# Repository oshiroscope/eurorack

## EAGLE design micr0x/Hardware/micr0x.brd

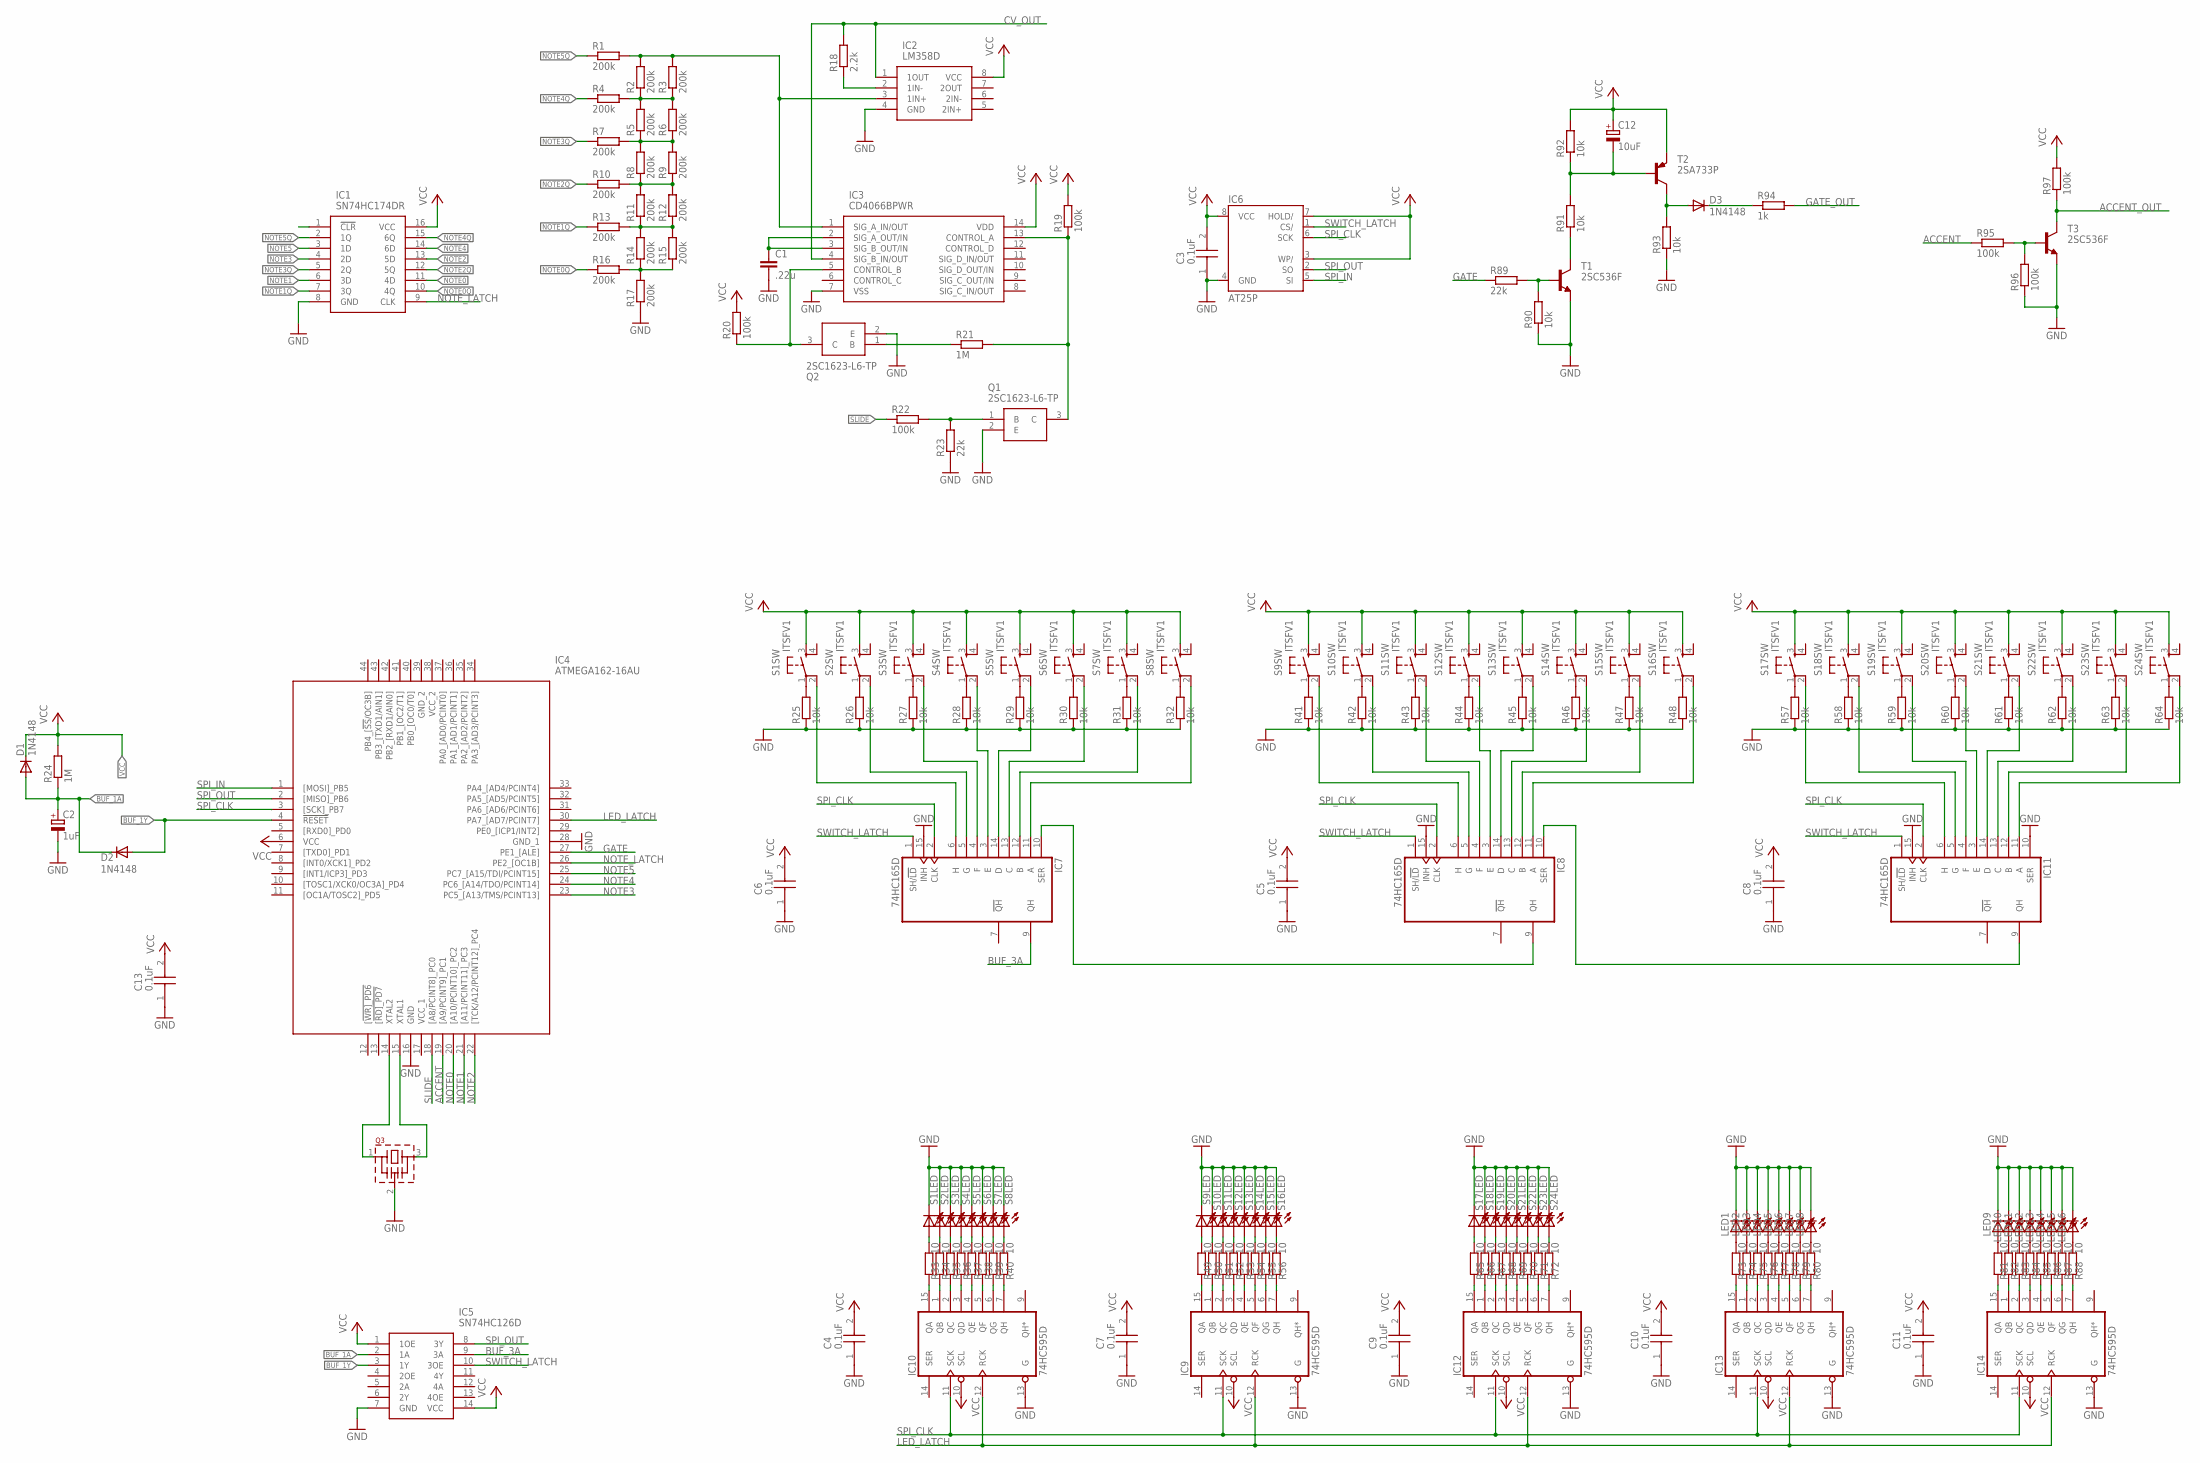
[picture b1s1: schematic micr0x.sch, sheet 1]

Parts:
C1: .22u; C075-032X103; MOUSER_PART_NUMBER QYX2A224KTP
C2: 1uF; E2-5; MOUSER_PART_NUMBER 140-REA1R0M2CBK0511P
C3, C4, C5, C6, C7, C8, C9, C10, C11, C13: 0.1uF; CAPC1608X90N
C12: 10uF; E2-5
D1, D2, D3: 1N4148; DO35-7
IC1: SN74HC174DR; SOIC127P600X175-16N
IC2: LM358D; SOIC127P600X175-8N
IC3: CD4066BPWR; SOP65P640X120-14N
IC4: ATMEGA162-16AU; QFP80P1200X1200X120-44N
IC5: SN74HC126D; SOIC127P600X175-14N
IC6: AT25P; DIL08
IC7, IC8, IC11: 74HC165D; SO16
IC9, IC10, IC12, IC13, IC14: 74HC595D; SO16
LED1, LED2, LED3, LED4, LED5, LED6, LED7, LED8, LED9, LED10, LED11, LED12, LED13, LED14, LED15, LED16: LED3MM
Q1, Q2: 2SC1623-L6-TP; SOT96P237X112-3N
Q3: CSTLS_X
R1, R2, R3, R4, R5, R6, R7, R8, R9, R10, R11, R12, R13, R14, R15, R16, R17: 200k; R0603; MOUSER_PART_NUMBER RCS0603200KFKEA
R18: 2.2k; R0603; MOUSER_PART_NUMBER RCS06032K20JNEA
R19, R20, R22: 100k; R0603; MOUSER_PART_NUMBER RCS0603100KJNEA
R21, R24: 1M; R0603; MOUSER_PART_NUMBER RCS06031M00JNEA
R23: 22k; R0603; MOUSER_PART_NUMBER RCS060322K0JNEA
R25, R26, R27, R28, R29, R30, R31, R32, R41, R42, R43, R44, R45, R46, R47, R48, R57, R58, R59, R60, R61, R62, R63, R64, R90, R91, R92, R93: 10k; R0603; MOUSER_PART_NUMBER RCS060310K0JNEA
R33, R34, R35, R36, R37, R38, R39, R40, R49, R50, R51, R52, R53, R54, R55, R56, R65, R66, R67, R68, R69, R70, R71, R72, R73, R74, R75, R76, R77, R78, R79, R80, R81, R82, R83, R84, R85, R86, R87, R88: 10; R0603; MOUSER_PART_NUMBER RCS0603200KFKEA
R89: 22k; R0603; MOUSER_PART_NUMBER RCS060310K0JNEA
R94: 1k; R0603; MOUSER_PART_NUMBER RCS060310K0JNEA
R95, R96, R97: 100k; R0603; MOUSER_PART_NUMBER RCS060310K0JNEA
S1, S2, S3, S4, S5, S6, S7, S8, S9, S10, S11, S12, S13, S14, S15, S16, S17, S18, S19, S20, S21, S22, S23, S24: ITSFV1
T1, T3: 2SC536F; TO92
T2: 2SA733P; TO92

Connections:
ACCENT: IC4.19 ([A9/PCINT9]_PC1), R95.1
ACCENT_OUT: R97.1, T3.3 (C)
BUF_1A: C2.+, D1.A, D2.C, IC5.2 (1A), R24.1
BUF_1Y: D2.A, IC4.4 (!RESET), IC5.3 (1Y)
BUF_3A: IC5.9 (3A), IC7.9 (QH)
CV_OUT: IC2.1 (1OUT), IC3.4 (SIG_B_IN/OUT), R18.2
GATE: IC4.27 (PE1_[ALE]), R89.1
GATE_OUT: R94.2
GND: C1.2, C2.-, C3.1, C4.1, C5.1, C6.1, C7.1, C8.1, C9.1, C10.1, C11.1, C13.1, IC1.8 (GND), IC2.4 (GND), IC3.7 (VSS), IC4.16 (GND), IC4.28 (GND_1), IC5.7 (GND), IC6.4 (GND), IC7.8 (GND), IC7.15 (INH), IC8.8 (GND), IC8.15 (INH), IC9.8 (GND), IC9.13 (G), IC10.8 (GND), IC10.13 (G), IC11.8 (GND), IC11.10 (SER), IC11.15 (INH), IC12.8 (GND), IC12.13 (G), IC13.8 (GND), IC13.13 (G), IC14.8 (GND), IC14.13 (G), LED1.K (C), LED2.K (C), LED3.K (C), LED4.K (C), LED5.K (C), LED6.K (C), LED7.K (C), LED8.K (C), LED9.K (C), LED10.K (C), LED11.K (C), LED12.K (C), LED13.K (C), LED14.K (C), LED15.K (C), LED16.K (C), Q1.2 (E), Q2.2 (E), Q3.2 (VSS), R17.1, R23.1, R25.1, R26.1, R27.1, R28.1, R29.1, R30.1, R31.1, R32.1, R41.1, R42.1, R43.1, R44.1, R45.1, R46.1, R47.1, R48.1, R57.1, R58.1, R59.1, R60.1, R61.1, R62.1, R63.1, R64.1, R90.1, R93.1, R96.1, S1.L1, S2.L1, S3.L1, S4.L1, S5.L1, S6.L1, S7.L1, S8.L1, S9.L1, S10.L1, S11.L1, S12.L1, S13.L1, S14.L1, S15.L1, S16.L1, S17.L1, S18.L1, S19.L1, S20.L1, S21.L1, S22.L1, S23.L1, S24.L1, T1.1 (E), T3.1 (E)
GND_2: IC4.39 (GND_2)
LED_LATCH: IC4.30 (PA7_[AD7/PCINT7]), IC9.12 (RCK), IC10.12 (RCK), IC12.12 (RCK), IC13.12 (RCK), IC14.12 (RCK)
unnamed: R2.1, R3.1, R4.2, R5.2, R6.2
unnamed: IC2.2 (1IN-), R18.1
unnamed: R5.1, R6.1, R7.2, R8.2, R9.2
unnamed: R8.1, R9.1, R10.2, R11.2, R12.2
unnamed: C1.1, IC3.2 (SIG_A_OUT/IN), IC3.3 (SIG_B_OUT/IN)
unnamed: R11.1, R12.1, R13.2, R14.2, R15.2
unnamed: IC3.13 (CONTROL_A), Q1.3 (C), R19.1, R21.2
unnamed: R14.1, R15.1, R16.2, R17.2
unnamed: IC2.3 (1IN+), IC3.1 (SIG_A_IN/OUT), R1.2, R2.2, R3.2
unnamed: Q2.1 (B), R21.1
unnamed: IC3.5 (CONTROL_B), Q2.3 (C), R20.1
unnamed: Q1.1 (B), R22.2, R23.2
unnamed: IC4.14 (XTAL2), Q3.1
unnamed: IC4.15 (XTAL1), Q3.3
unnamed: IC7.6 (H), S1.2
unnamed: IC7.5 (G), S2.2
unnamed: IC7.4 (F), S3.2
unnamed: IC7.3 (E), S4.2
unnamed: IC7.11 (A), S8.2
unnamed: IC7.12 (B), S7.2
unnamed: IC7.13 (C), S6.2
unnamed: IC7.14 (D), S5.2
unnamed: R25.2, S1.1
unnamed: R26.2, S2.1
unnamed: R27.2, S3.1
unnamed: R28.2, S4.1
unnamed: R29.2, S5.1
unnamed: R30.2, S6.1
unnamed: R31.2, S7.1
unnamed: R32.2, S8.1
unnamed: R33.2, S1.L2
unnamed: R34.2, S2.L2
unnamed: R35.2, S3.L2
unnamed: R36.2, S4.L2
unnamed: R37.2, S5.L2
unnamed: R38.2, S6.L2
unnamed: R39.2, S7.L2
unnamed: R40.2, S8.L2
unnamed: IC10.7 (QH), R40.1
unnamed: IC10.6 (QG), R39.1
unnamed: IC10.5 (QF), R38.1
unnamed: IC10.4 (QE), R37.1
unnamed: IC10.3 (QD), R36.1
unnamed: IC10.2 (QC), R35.1
unnamed: IC10.1 (QB), R34.1
unnamed: IC10.15 (QA), R33.1
unnamed: IC8.6 (H), S9.2
unnamed: IC8.5 (G), S10.2
unnamed: IC8.4 (F), S11.2
unnamed: IC8.3 (E), S12.2
unnamed: IC8.11 (A), S16.2
unnamed: IC8.12 (B), S15.2
unnamed: IC8.13 (C), S14.2
unnamed: IC8.14 (D), S13.2
unnamed: R41.2, S9.1
unnamed: R42.2, S10.1
unnamed: R43.2, S11.1
unnamed: R44.2, S12.1
unnamed: R45.2, S13.1
unnamed: R46.2, S14.1
unnamed: R47.2, S15.1
unnamed: R48.2, S16.1
unnamed: IC7.10 (SER), IC8.9 (QH)
unnamed: IC8.10 (SER), IC11.9 (QH)
unnamed: R49.2, S9.L2
unnamed: R50.2, S10.L2
unnamed: R51.2, S11.L2
unnamed: R52.2, S12.L2
unnamed: R53.2, S13.L2
unnamed: R54.2, S14.L2
unnamed: R55.2, S15.L2
unnamed: R56.2, S16.L2
unnamed: IC9.7 (QH), R56.1
unnamed: IC9.6 (QG), R55.1
unnamed: IC9.5 (QF), R54.1
unnamed: IC9.4 (QE), R53.1
unnamed: IC9.3 (QD), R52.1
unnamed: IC9.2 (QC), R51.1
unnamed: IC9.1 (QB), R50.1
unnamed: IC9.15 (QA), R49.1
unnamed: IC11.6 (H), S17.2
unnamed: IC11.5 (G), S18.2
unnamed: IC11.4 (F), S19.2
unnamed: IC11.3 (E), S20.2
unnamed: IC11.11 (A), S24.2
unnamed: IC11.12 (B), S23.2
unnamed: IC11.13 (C), S22.2
unnamed: IC11.14 (D), S21.2
unnamed: R57.2, S17.1
unnamed: R58.2, S18.1
unnamed: R59.2, S19.1
unnamed: R60.2, S20.1
unnamed: R61.2, S21.1
unnamed: R62.2, S22.1
unnamed: R63.2, S23.1
unnamed: R64.2, S24.1
unnamed: IC13.7 (QH), R80.1
unnamed: R65.2, S17.L2
unnamed: R66.2, S18.L2
unnamed: R67.2, S19.L2
unnamed: R68.2, S20.L2
unnamed: R69.2, S21.L2
unnamed: R70.2, S22.L2
unnamed: R71.2, S23.L2
unnamed: R72.2, S24.L2
unnamed: IC12.7 (QH), R72.1
unnamed: IC12.6 (QG), R71.1
unnamed: IC12.5 (QF), R70.1
unnamed: IC12.4 (QE), R69.1
unnamed: IC12.3 (QD), R68.1
unnamed: IC12.2 (QC), R67.1
unnamed: IC12.1 (QB), R66.1
unnamed: IC12.15 (QA), R65.1
unnamed: IC13.6 (QG), R79.1
unnamed: IC13.5 (QF), R78.1
unnamed: IC13.4 (QE), R77.1
unnamed: IC13.3 (QD), R76.1
unnamed: IC13.2 (QC), R75.1
unnamed: IC13.1 (QB), R74.1
unnamed: IC13.15 (QA), R73.1
unnamed: LED1.A, R73.2
unnamed: LED2.A, R74.2
unnamed: LED3.A, R75.2
unnamed: LED4.A, R76.2
unnamed: LED5.A, R77.2
unnamed: LED6.A, R78.2
unnamed: LED7.A, R79.2
unnamed: LED8.A, R80.2
unnamed: IC14.7 (QH), R88.1
unnamed: IC14.6 (QG), R87.1
unnamed: IC14.5 (QF), R86.1
unnamed: IC14.4 (QE), R85.1
unnamed: IC14.3 (QD), R84.1
unnamed: IC14.2 (QC), R83.1
unnamed: IC14.1 (QB), R82.1
unnamed: IC14.15 (QA), R81.1
unnamed: LED9.A, R81.2
unnamed: LED10.A, R82.2
unnamed: LED11.A, R83.2
unnamed: LED12.A, R84.2
unnamed: LED13.A, R85.2
unnamed: LED14.A, R86.2
unnamed: LED15.A, R87.2
unnamed: LED16.A, R88.2
unnamed: C12.-, R91.2, R92.1, T2.2 (B)
unnamed: R91.1, T1.3 (C)
unnamed: R89.2, R90.2, T1.2 (B)
unnamed: D3.A, R93.2, T2.3 (C)
unnamed: D3.C, R94.1
unnamed: R95.2, R96.2, T3.2 (B)
NOTE0: IC1.11 (4D), IC4.20 ([A10/PCINT10]_PC2)
NOTE0Q: IC1.10 (4Q), R16.1
NOTE1: IC1.6 (3D), IC4.21 ([A11/PCINT11]_PC3)
NOTE1Q: IC1.7 (3Q), R13.1
NOTE2: IC1.13 (5D), IC4.22 ([TCK/A12/PCINT12]_PC4)
NOTE2Q: IC1.12 (5Q), R10.1
NOTE3: IC1.4 (2D), IC4.23 (PC5_[A13/TMS/PCINT13])
NOTE3Q: IC1.5 (2Q), R7.1
NOTE4: IC1.14 (6D), IC4.24 (PC6_[A14/TDO/PCINT14])
NOTE4Q: IC1.15 (6Q), R4.1
NOTE5: IC1.3 (1D), IC4.25 (PC7_[A15/TDI/PCINT15])
NOTE5Q: IC1.2 (1Q), R1.1
NOTE_LATCH: IC1.9 (CLK), IC4.26 (PE2_[OC1B])
SLIDE: IC4.18 ([A8/PCINT8]_PC0), R22.1
SPI_CLK: IC4.3 ([SCK]_PB7), IC6.6 (SCK), IC7.2 (CLK), IC8.2 (CLK), IC9.11 (SCK), IC10.11 (SCK), IC11.2 (CLK), IC12.11 (SCK), IC13.11 (SCK), IC14.11 (SCK)
SPI_IN: IC4.1 ([MOSI]_PB5), IC6.5 (SI)
SPI_OUT: IC4.2 ([MISO]_PB6), IC5.8 (3Y), IC6.2 (SO)
SWITCH_LATCH: IC5.10 (3OE), IC6.1 (CS/), IC7.1 (SH/!LD), IC8.1 (SH/!LD), IC11.1 (SH/!LD)
VCC: C3.2, C4.2, C5.2, C6.2, C7.2, C8.2, C9.2, C10.2, C11.2, C12.+, C13.2, D1.C, IC1.16 (VCC), IC2.8 (VCC), IC3.14 (VDD), IC4.6 (VCC), IC5.1 (1OE), IC5.14 (VCC), IC6.3 (WP/), IC6.7 (HOLD/), IC6.8 (VCC), IC7.16 (VCC), IC8.16 (VCC), IC9.10 (SCL), IC9.16 (VCC), IC10.10 (SCL), IC10.16 (VCC), IC11.16 (VCC), IC12.10 (SCL), IC12.16 (VCC), IC13.10 (SCL), IC13.16 (VCC), IC14.10 (SCL), IC14.16 (VCC), R19.2, R20.2, R24.2, R92.2, R97.2, S1.3, S2.3, S3.3, S4.3, S5.3, S6.3, S7.3, S8.3, S9.3, S10.3, S11.3, S12.3, S13.3, S14.3, S15.3, S16.3, S17.3, S18.3, S19.3, S20.3, S21.3, S22.3, S23.3, S24.3, T2.1 (E)
VCC_1: IC4.17 (VCC_1)
VCC_2: IC4.38 (VCC_2)

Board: 2 copper layers, 173 parts (1 on the bottom side), 178 nets, no tracks yet.

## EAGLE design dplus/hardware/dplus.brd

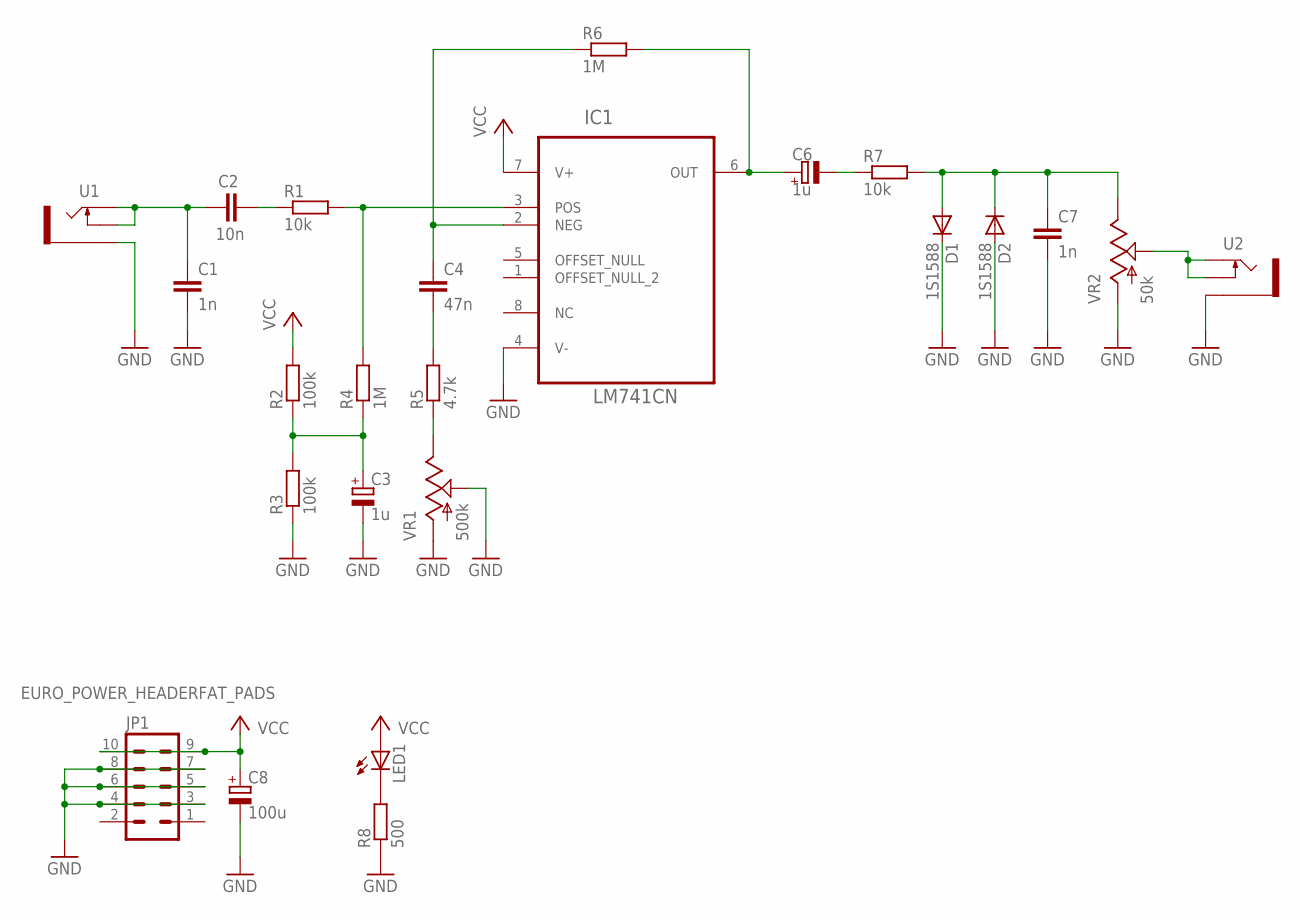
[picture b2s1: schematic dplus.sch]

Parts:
C1, C7: 1n; C050-025X075
C2: 10n; C050-035X075
C3, C6: 1u; E2,5-5
C4: 47n; C050-045X075
C8: 100u; E2-4
D1, D2: 1S1588; D-5
IC1: LM741CN; DIP254P762X508-8
JP1: EURO_POWER_HEADERFAT_PADS; EURO_PWR_HEADER_FAT
LED1: LED3MM
R1, R7: 10k; R1206W
R2, R3: 100k; R1206W
R4, R6: 1M; R1206W
R5: 4.7k; R1206W
R8: 500; R1206W
U1, U2: THONKICONNOLD; THONKICONN
VR1: 500k; 9MM_SNAP-IN_POT
VR2: 50k; 9MM_SNAP-IN_POT

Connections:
GND: C1.2, C3.-, C7.2, C8.-, D1.C, D2.A, IC1.4 (V-), JP1.3, JP1.4, JP1.5, JP1.6, JP1.7, JP1.8, R3.1, R8.1, U1.P$1_SLEEVE (SLEEVE), U2.P$1_SLEEVE (SLEEVE), VR1.1 (A), VR1.2 (S), VR2.1 (A)
unnamed: C2.2, R1.1
unnamed: C1.1, C2.1, U1.P$2_SWITCH (SWITCH), U1.P$3_TIP (TIP)
unnamed: C3.+, R2.1, R3.2, R4.1
unnamed: IC1.3 (POS), R1.2, R4.2
unnamed: C4.1, IC1.2 (NEG), R6.1
unnamed: C6.+, IC1.6 (OUT), R6.2
unnamed: C4.2, R5.2
unnamed: C7.1, D1.A, D2.C, R7.2, VR2.3 (E)
unnamed: C6.-, R7.1
unnamed: R5.1, VR1.3 (E)
unnamed: U2.P$2_SWITCH (SWITCH), U2.P$3_TIP (TIP), VR2.2 (S)
unnamed: LED1.K (C), R8.2
VCC: C8.+, IC1.7 (V+), JP1.9, JP1.10, LED1.A, R2.2

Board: 2 copper layers, 24 parts (0 on the bottom side), 14 nets, no tracks yet.

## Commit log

2019-01-12 add dplus: eurorack distortion and micr0x: x0xb0x-based 1U sequencer
2019-01-21 added interface section
2019-01-24 add components
2019-02-16 add change
